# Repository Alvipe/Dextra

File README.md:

# Dextra
Dextra is a printable robotic hand with the size of a human hand. This project was initially started to build a replicable and low cost alternative to current robotic hand prostheses. However, I think this device has more potential uses, for example in robotics research (humanoid robotics, mobile platforms with manipulation capabilities) or in education, fields that could benefit from the existence of a cheap and easy to repair robotic hand, a robotic device that is replicable and hackable, and simple but functional.

The key design points of Dextra are: adaptive grip, compact size, mechanical simplicity and ease of replication. The mechanical design of Dextra revolves around the finger module the finger module, a modular part that comprises a compact linear actuator based on the Pololu 1000:1 Micro Metal Gearmotor HP, position feedback provided by a magnetic encoder, and the mechanical printable finger. This module is used in the four fingers of the hand, and the thumb is a variation of the same design. This makes assembly and repair simpler. Modular design also may favour the possibility of modifying the original design.

To reduce the size, as well as the mechanical complexity of Dextra, the fingers are underactuated, that is, they have more degrees of freedom (DOF) than actuators. Each finger module has three DOF and one motor, while the thumb has two DOF and one motor. Besides that, the abduction/adduction of the thumb is independently actuated by a RC servomotor.

The motion of the fingers of Dextra is controlled by a position control loop. Since the finger is underactuated, the angular position of each phalanx cannot be controlled independently. Instead, the total angular position of the finger, that is, the sum of the three joint angles, is controlled. Each finger is controlled by a PID loop that takes a position setpoint as the input and uses the feedback position measured by a magnetic quadrature encoder to adjust the real position of the DC motor driving the finger.

Dextra can be controlled either by sending commands from a computer with a GUI, or by using EMG signals, as would be done if the hand is used as a prosthesis. To implement the second type of control, an EMG interface called [Mumai](https://github.com/Alvipe/Mumai) is being used. Currently, a myoelectric threshold controller is implemented: the raw EMG signal provided by the EMG interface is rectified and smoothed by software and when this processed signal exceeds a certain value, the hand closes.

Here are some videos showing how Dextra works:
* [Open-loop finger control](https://www.youtube.com/watch?v=N3UU5vtAwHg)
* [Closed-loop finger control](https://www.youtube.com/watch?v=Uz6x0zFXkCc)
* [Myoelectric control](https://www.youtube.com/watch?v=L_VyQa0jCiI)

There is more information about Dextra on its [hackaday.io project page](https://hackaday.io/project/9890-dextra).

# Assembly instructions
The assembly instructions can be found [here](https://github.com/Alvipe/Dextra/tree/master/doc/dextra_assembly_instructions.pdf).

# Project index
* [Control](https://github.com/Alvipe/Dextra/tree/master/Control) - Code for different control methods (EMG, GUI)
* [Firmware](https://github.com/Alvipe/Dextra/tree/master/Firmware) - Main program and libraries that make Dextra move
* [Parts](https://github.com/Alvipe/Dextra/tree/master/Parts) - STL files of the printable parts of Dextra and its corresponding FreeCAD source files
* [doc](https://github.com/Alvipe/Dextra/tree/master/doc) - Documentation files

# License

Code is licensed under the [GPL v3 License](https://www.gnu.org/licenses/gpl-3.0.html). The rest of the work is licensed under the [Creative Commons Attribution-ShareAlike 4.0 International License](http://creativecommons.org/licenses/by-sa/4.0/).

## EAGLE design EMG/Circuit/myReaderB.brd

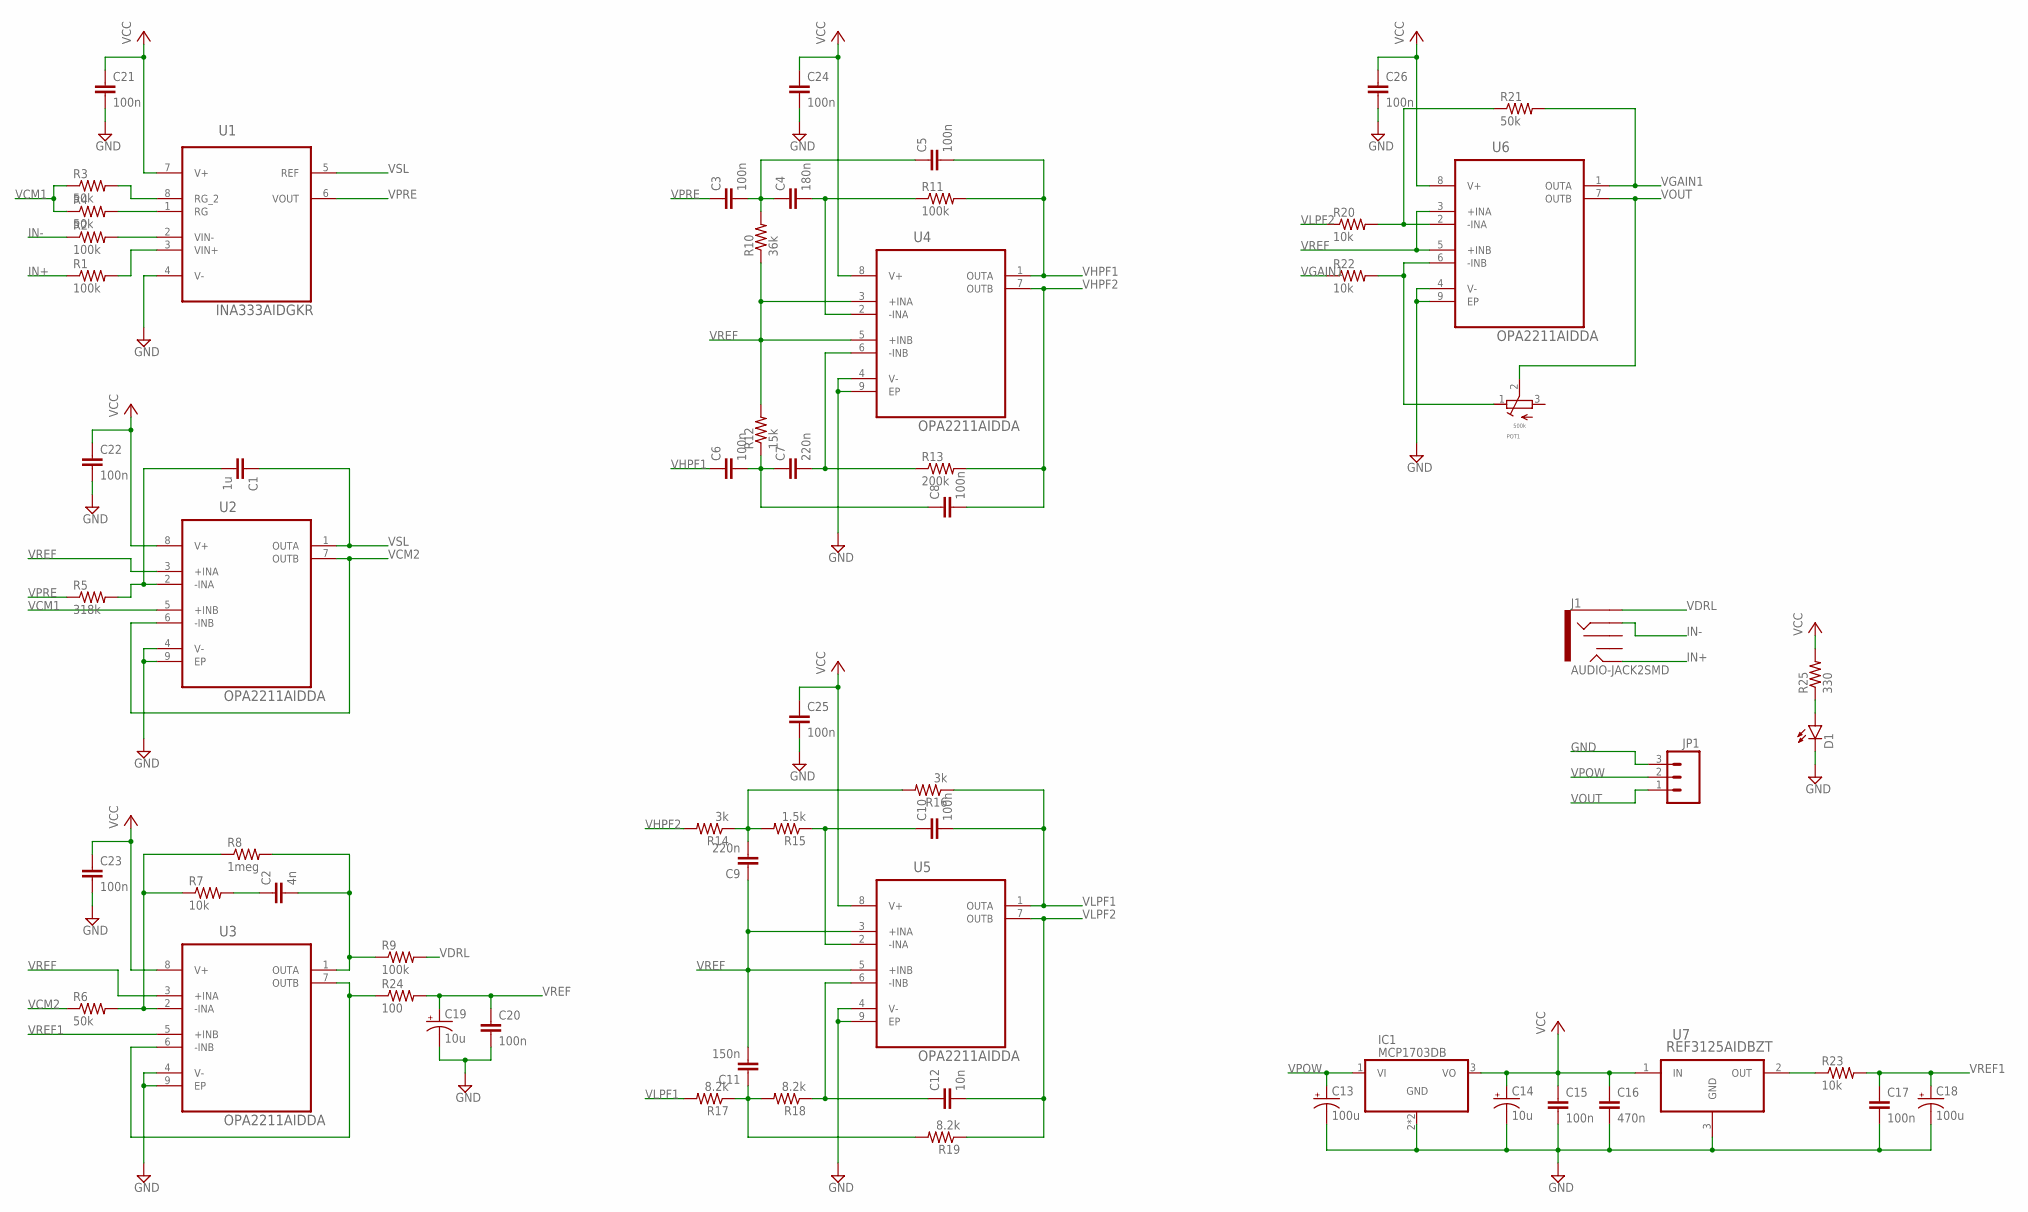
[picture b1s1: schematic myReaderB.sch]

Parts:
C1: 1u; 0402-CAP
C2: 4n; 0402-CAP
C3, C5, C6, C8, C10, C15, C17, C20, C21, C22, C23, C24, C25, C26: 100n; 0402-CAP
C4: 180n; 0402-CAP
C7, C9: 220n; 0402-CAP
C11: 150n; 0402-CAP
C12: 10n; 0402-CAP
C13, C18: 100u; EIA3216
C14, C19: 10u; EIA3216
C16: 470n; 0402-CAP
D1: LED0603; LED-0603
IC1: MCP1703DB; SOT223
J1: AUDIO-JACK2SMD; AUDIO-JACK-3.5MM-SMD
JP1: M03PTH; 1X03
POT1: 500k; BOURN_SMD_POTENTIOMETER
R1, R2, R9, R11: 100k; 0402-RES
R3, R4, R6, R21: 50k; 0402-RES
R5: 318k; 0402-RES
R7, R20, R22, R23: 10k; 0402-RES
R8: 1meg; 0402-RES
R10: 36k; 0402-RES
R12: 15k; 0402-RES
R13: 200k; 0402-RES
R14, R16: 3k; 0402-RES
R15: 1.5k; 0402-RES
R17, R18, R19: 8.2k; 0402-RES
R24: 100; 0402-RES
R25: 330; 0402-RES
U1: INA333AIDGKR; SOP65P490X110-8N
U2, U3, U4, U5, U6: OPA2211AIDDA; SOIC127P600X170-9N
U7: REF3125AIDBZT; SOT95P237X112-3N

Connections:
GND: C13.C (-), C14.C (-), C15.2, C16.2, C17.2, C18.C (-), C19.C (-), C20.2, C21.2, C22.2, C23.2, C24.2, C25.2, C26.2, D1.C, IC1.2 (GND), IC1.4 (GND), JP1.3, U1.4 (V-), U2.4 (V-), U2.9 (EP), U3.4 (V-), U3.9 (EP), U4.4 (V-), U4.9 (EP), U5.4 (V-), U5.9 (EP), U6.4 (V-), U6.9 (EP), U7.3 (GND)
IN+: J1.TIP, R1.1
IN-: J1.RING, R2.1
unnamed: R1.2, U1.3 (VIN+)
unnamed: R2.2, U1.2 (VIN-)
unnamed: R20.2, R21.1, U6.2 (-INA)
unnamed: R4.2, U1.1 (RG)
unnamed: R6.2, R7.1, R8.1, U3.2 (-INA)
unnamed: C1.2, R5.2, U2.2 (-INA)
unnamed: C4.2, R11.1, U4.2 (-INA)
unnamed: C2.1, R7.2
unnamed: C2.2, R8.2, R9.1, U3.1 (OUTA)
unnamed: C3.2, C4.1, C5.1, R10.2
unnamed: C10.1, R15.1, U5.2 (-INA)
unnamed: C9.2, R14.1, R15.2, R16.2
unnamed: C7.2, R13.1, U4.6 (-INB)
unnamed: C6.2, C7.1, C8.1, R12.1
unnamed: C12.1, R18.1, U5.6 (-INB)
unnamed: C11.1, R17.1, R18.2, R19.2
unnamed: R3.2, U1.8 (RG_2)
unnamed: D1.A, R25.1
unnamed: POT1.1 (A), R22.2, U6.6 (-INB)
unnamed: R24.1, U3.6 (-INB), U3.7 (OUTB)
unnamed: R23.1, U7.2 (OUT)
VCC: C14.A (+), C15.1, C16.1, C21.1, C22.1, C23.1, C24.1, C25.1, C26.1, IC1.3 (VO), R25.2, U1.7 (V+), U2.8 (V+), U3.8 (V+), U4.8 (V+), U5.8 (V+), U6.8 (V+), U7.1 (IN)
VCM1: R3.1, R4.1, U2.5 (+INB)
VCM2: R6.1, U2.6 (-INB), U2.7 (OUTB)
VDRL: J1.SLEEVE, R9.2
VGAIN1: R21.2, R22.1, U6.1 (OUTA)
VHPF1: C5.2, C6.1, R11.2, U4.1 (OUTA)
VHPF2: C8.2, R13.2, R14.2, U4.7 (OUTB)
VLPF1: C10.2, R16.1, R17.2, U5.1 (OUTA)
VLPF2: C12.2, R19.1, R20.1, U5.7 (OUTB)
VOUT: JP1.1, POT1.2 (S), U6.7 (OUTB)
VPOW: C13.A (+), IC1.1 (VI), JP1.2
VPRE: C3.1, R5.1, U1.6 (VOUT)
VREF: C9.1, C11.2, C19.A (+), C20.1, R10.1, R12.2, R24.2, U2.3 (+INA), U3.3 (+INA), U4.3 (+INA), U4.5 (+INB), U5.3 (+INA), U5.5 (+INB), U6.3 (+INA), U6.5 (+INB)
VREF1: C17.1, C18.A (+), R23.2, U3.5 (+INB)
VSL: C1.1, U1.5 (REF), U2.1 (OUTA)

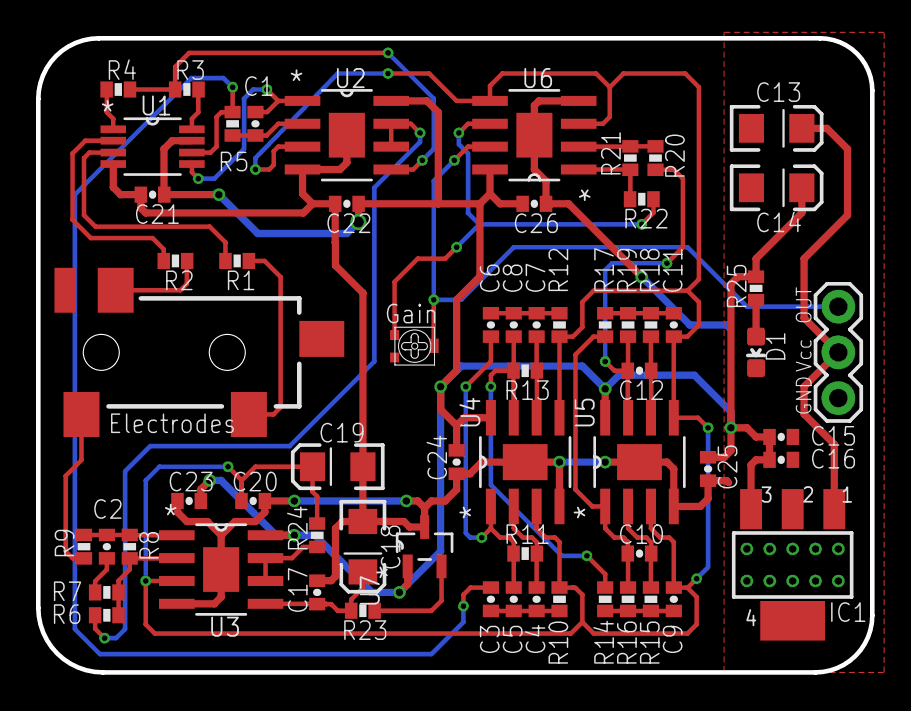
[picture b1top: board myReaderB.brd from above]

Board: 2 copper layers, 46.3 x 35.2 mm, 64 parts (1 on the bottom side), 39 nets.

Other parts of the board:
U$1: BQ_LOGO

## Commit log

2016-01-07 Hand parts added
2016-01-07 .stl added
2016-01-07 FreeCAD directory added
2016-01-08 EMG circuit files added
2016-01-08 Update README.md and project structure
2016-01-08 Added Python code (proof of concept) to classify gestures from EMG signals
2016-01-08 Added actuated thumb abduction
2016-01-11 Modified abductor and dorsal
2016-01-12 Added code to control a finger
2016-01-21 Added palm and update dorsal
2016-01-27 Update parts
2016-01-27 Remove Freecad backup files
2016-02-17 Update finger_control.ino to control the finger position with a PID
2016-02-17 Modified abductor and palm
2016-02-19 Update finger module to use a Pololu 1000:1 micromotor
2016-02-20 Update thumb module and abductor
2016-02-22 Update palm and dorsal
2016-02-23 Update finger module
2016-02-24 Update thumb module
2016-02-24 Update distal and middle
2016-02-25 Update abductor
2016-02-26 Update project structure
2016-02-26 Deleted .pioenvs
2016-02-26 Update assembly
2016-03-02 Update finger_control.ino and send_position.py to control all the fingers
2016-03-11 Added data.json
2016-03-11 Update send_position.py to autodetect USB port
2016-03-14 Edit data.json
2016-05-11 Added firmware for ST Nucleo board
2016-05-11 Added instructions to upload the firmware and control the hand
2016-06-11 Added test code to control the finger force with a PID
2016-06-12 Update .travis.yml for all firmwares
2016-07-14 Added control folder
2016-07-14 Added Python script to control Dextra with a Leap Motion
2016-07-15 Renamed Teensy firmware to make it compatible with Arduino IDE
2016-07-16 Created library to control fingers
2016-07-19 Testing Travis integration
2016-07-19 Update firmware readme
2016-07-26 Added code to receive finger position array
2016-07-27 Update main.ino and add communication script
2016-07-27 Integrate Synapse library
2016-07-27 Update PC control script
2016-07-28 Update comm protocol
2016-07-28 Update Python comm script
2016-08-16 Integrated Synapse library
2016-08-16 Removed test firmwares
2016-08-16 Added a simple Kivy interface to send position commands
2016-08-19 Update control interface
2016-08-24 Remove experimental parts
2016-08-24 Update control and firmware readmes
2016-08-28 Added instructions to use the GUI
2016-08-28 Fixed image paths
2016-09-01 Rename Kivy file to work in Linux
2016-09-06 Added assembly instructions
2016-09-09 Added buttons to increment/decrement position
2016-09-13 Integrate Synapse module into GUI
2016-09-14 Update parts to integrate a wrist
    A wrist part has been added to allow the integration of the hand into a prosthesis socket, a robotic arm or simply a stand.
    The servo housing is now a separate part to allow the installation of the servo without interfering with the wrist.
    The abductor hinge has been widened a little to be able to use it with the new servo housing.
    The dorsal and palm parts have been updated to integrate the new wrist and servo housing parts.
    The hand assembly has been updated to reflect the new changes.
2016-09-16 Change finger position limits
2016-09-16 Refactor Finger library code
    Changed move() to writePosition() and getPos() to readPosition().
    The direction of the motor has been inverted in positionPID() by writing a LOW value to the phase pin when the control signal is positive and a HIGH value when the control signal is negative.
2016-09-16 Change finger pins
    The pins of the microcontroller to which the fingers are connected have been changed to be compatible with a new control board that includes the microcontroller and the motor drivers.
    The if-else condition that turned on and off a LED if a certain value was sent has been removed because its only purpose was to debug the code without using the hand.
    All move() functions have been renamed to writePosition() to comply with the refactored Finger library.
2016-09-19 Update parts (FreeCAD src and stls)
2016-09-19 Add a stand to put the hand in a vertical position
2016-10-02 Update control GUI
    Instead of sending the setpoint list every 100 ms, function send_setpoint_list() is now called only when there is a change in any of the position values. In this way the computational load of the han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
2016-10-02 Move control GUI files to a specific folder
2016-10-02 Add experimental EMG control firmware
2018-03-16 Add parts for left hand

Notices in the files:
parts and their libraries:
SparkFun-Passives: Licensing: Creative Commons ShareAlike 4.0 International - https://creativecommons.org/licenses/by-sa/4.0
